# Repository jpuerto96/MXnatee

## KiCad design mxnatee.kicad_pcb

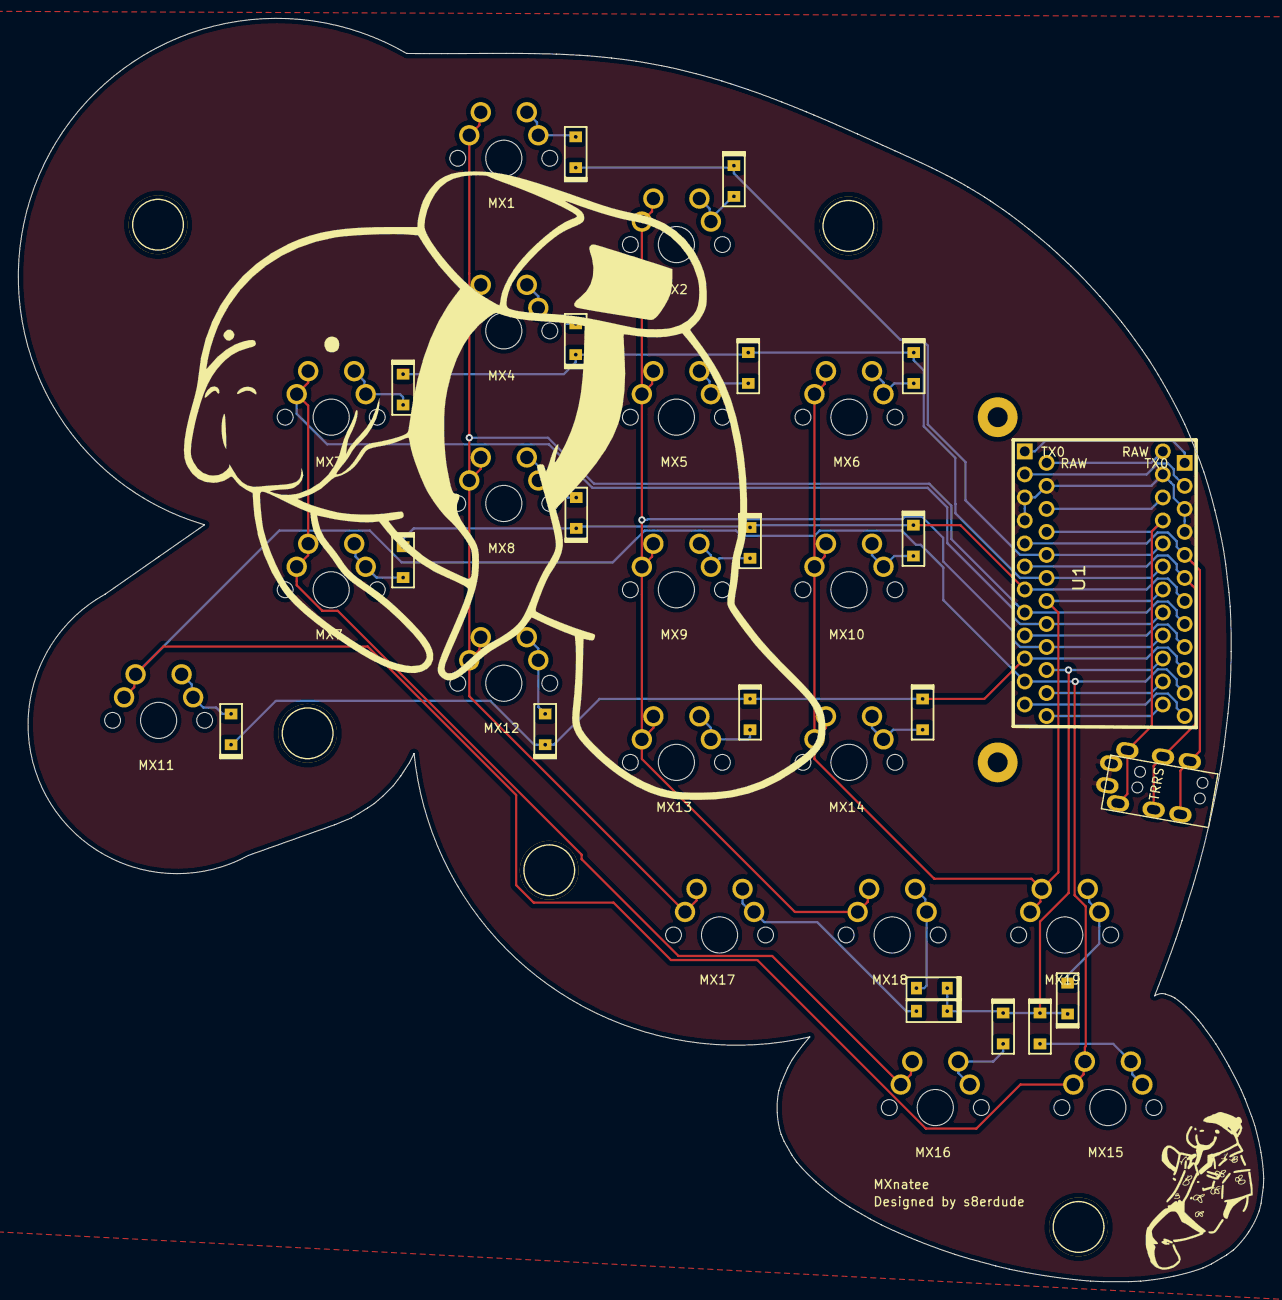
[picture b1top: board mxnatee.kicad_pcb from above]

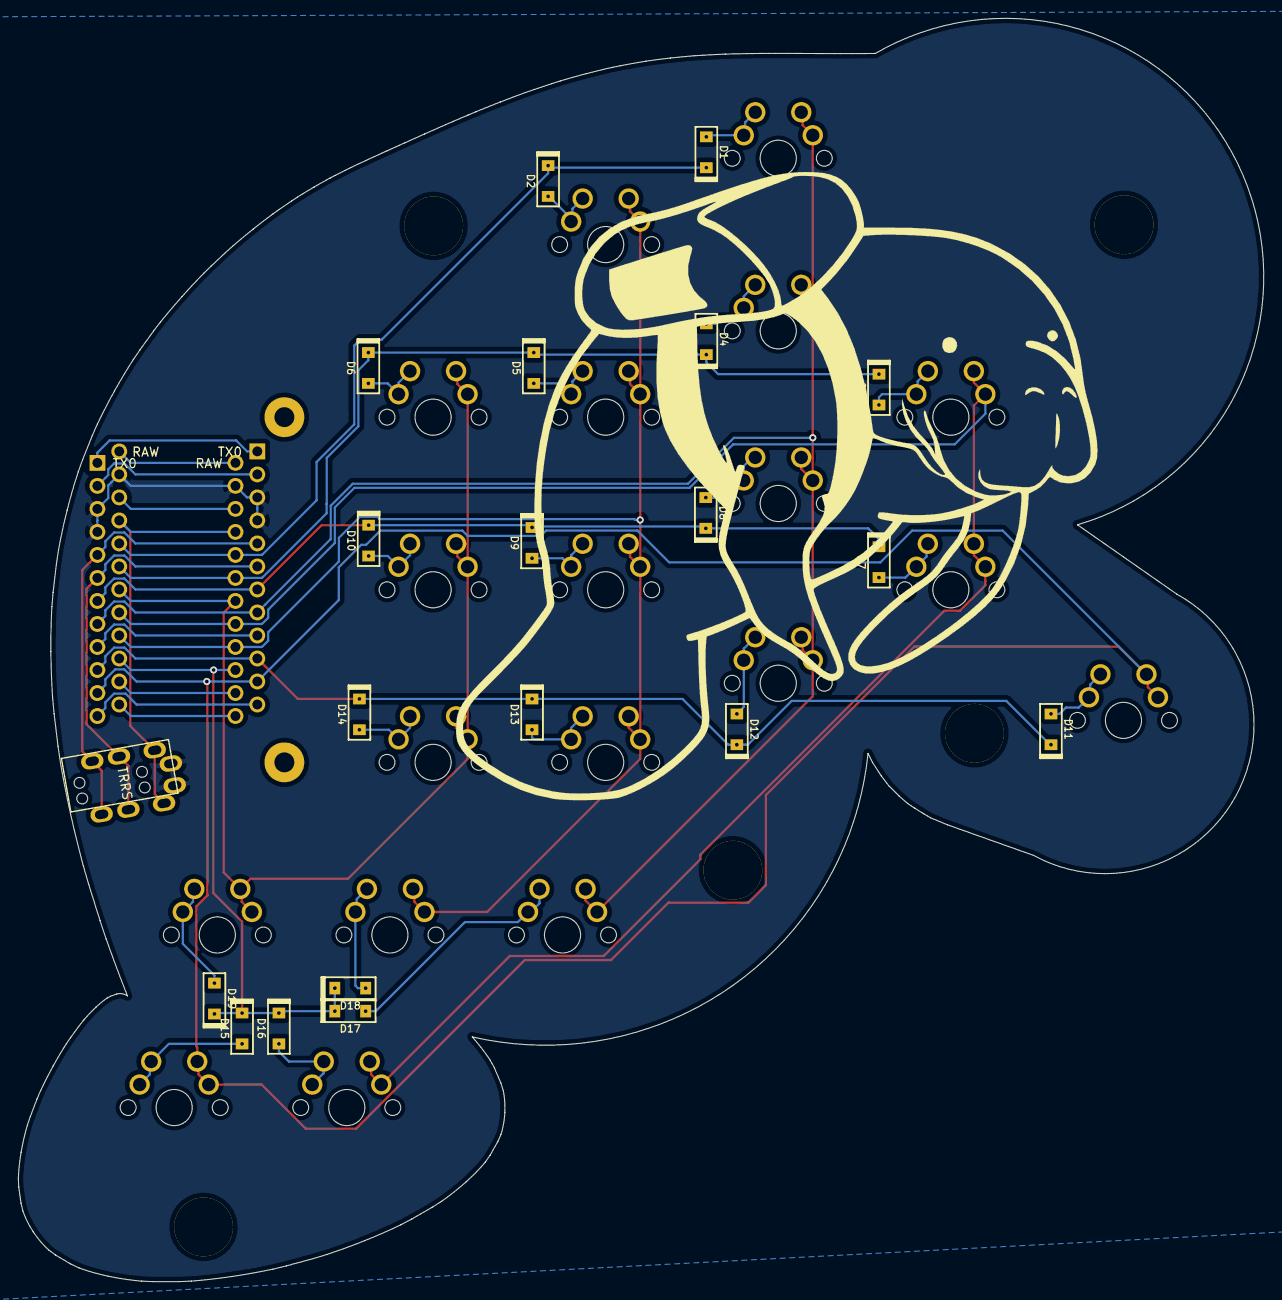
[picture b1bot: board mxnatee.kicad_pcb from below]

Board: 2 copper layers, 137.5 x 139.4 mm, 45 parts (19 on the bottom side), 33 nets.

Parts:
D1, D2, D3, D4, D5, D6, D7, D8, D9, D10, D11, D12, D13, D14, D15, D16, D17, D18, D19: D_Small; D_SOD123_thruhole
MX1, MX2, MX3, MX4, MX5, MX6, MX7, MX8, MX9, MX10, MX11, MX12, MX13, MX14, MX15, MX16, MX17, MX18, MX19: MX-NoLED; MX-NoLED-Reversible
U1: ProMicro; ArduinoProMicro-Reversible
U2: TRRS; MJ-4PP-9
U4, U4#2, U4#3, U4#4, U4#5: HOLE; MountingHole

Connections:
COL0: MX11.1, MX15.1, U1.11
COL1: MX3.1, MX7.1, MX16.1, U1.17
COL2: MX1.1, MX4.1, MX8.1, MX12.1, MX17.1, U1.8
COL3: MX2.1, MX5.1, MX9.1, MX13.1, MX18.1, U1.16
COL4: MX6.1, MX10.1, MX14.1, MX19.1, U1.18
DATA1: U1.6, U2.3
DATA2: U1.5, U2.4
GND: U1.3, U1.4, U1.23, U2.1
unnamed: D1.2, MX1.2
unnamed: D2.2, MX2.2
unnamed: D3.2, MX3.2
unnamed: D4.2, MX4.2
unnamed: D5.2, MX5.2
unnamed: D6.2, MX6.2
unnamed: D7.2, MX7.2
unnamed: D8.2, MX8.2
unnamed: D9.2, MX9.2
unnamed: D10.2, MX10.2
unnamed: D11.2, MX11.2
unnamed: D12.2, MX12.2
unnamed: D13.2, MX13.2
unnamed: D14.2, MX14.2
unnamed: D15.2, MX15.2
unnamed: D16.2, MX16.2
unnamed: D17.2, MX17.2
unnamed: D18.2, MX18.2
unnamed: D19.2, MX19.2
ROW0: D1.1, D2.1, U1.20
ROW1: D3.1, D4.1, D5.1, D6.1, U1.19
ROW2: D7.1, D8.1, D9.1, D10.1, U1.7
ROW3: D11.1, D12.1, D13.1, D14.1, U1.10
ROW4: D15.1, D16.1, D17.1, D18.1, D19.1, U1.15
VCC: U1.21, U2.2

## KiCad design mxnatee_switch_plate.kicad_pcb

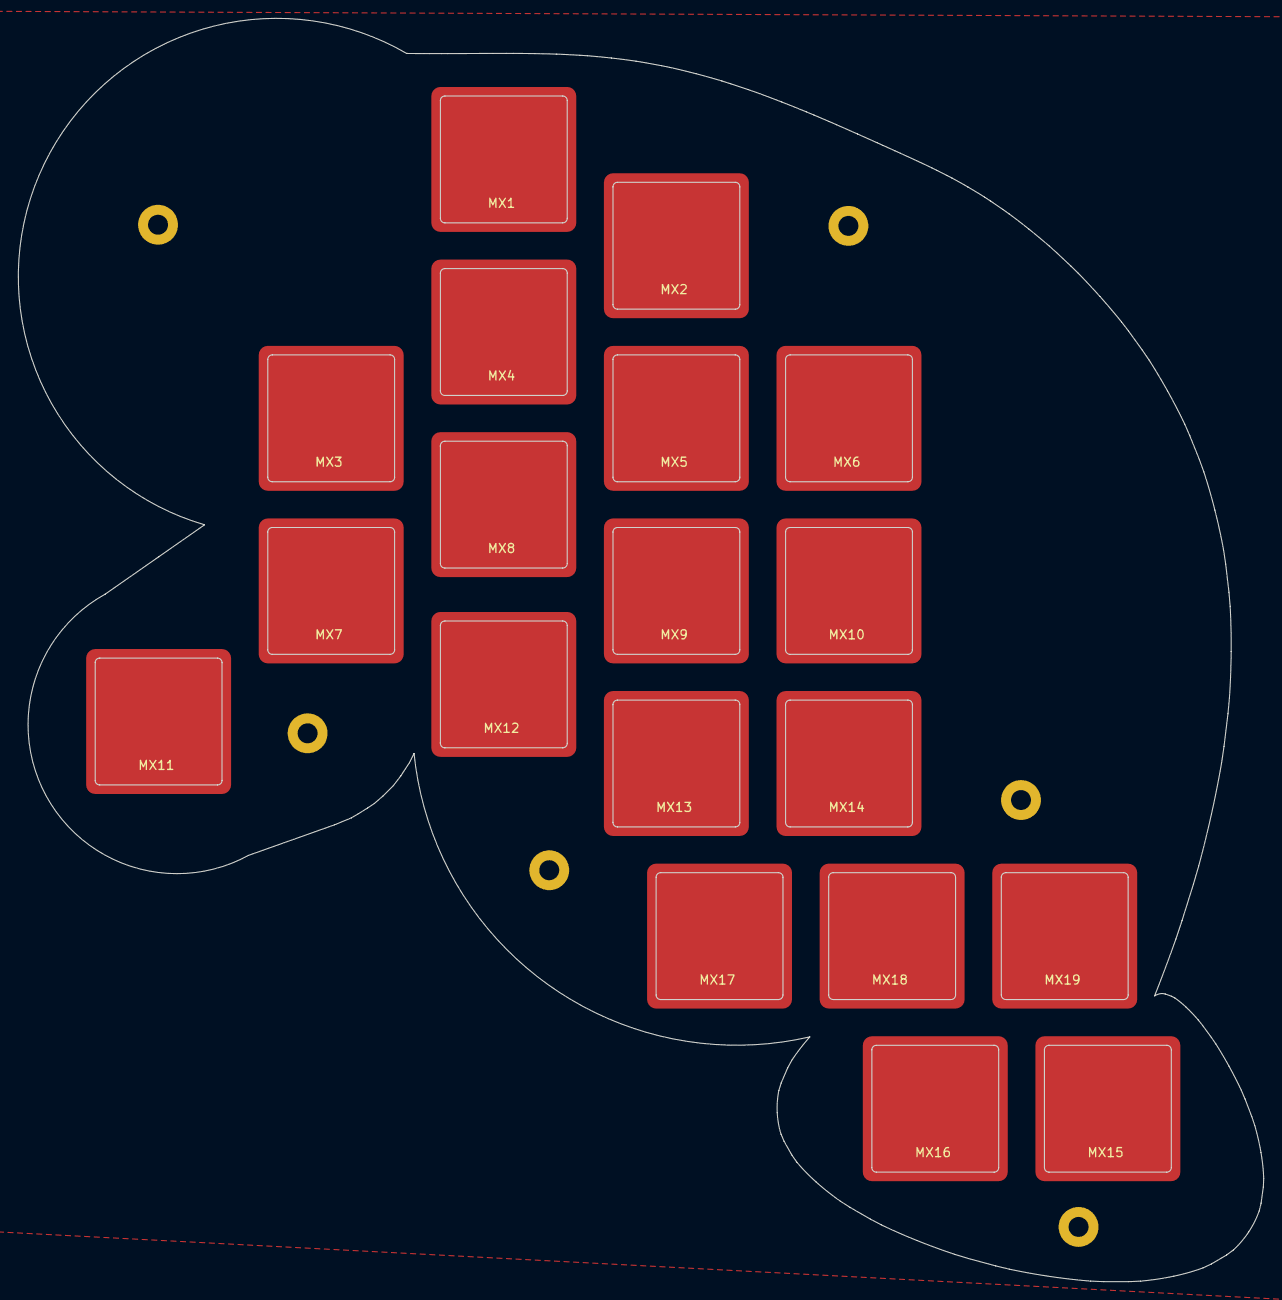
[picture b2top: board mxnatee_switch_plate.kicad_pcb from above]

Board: 2 copper layers, 137.5 x 139.4 mm, 25 parts (0 on the bottom side), 5 nets, no tracks yet.

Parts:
MX1, MX2, MX3, MX4, MX5, MX6, MX7, MX8, MX9, MX10, MX11, MX12, MX13, MX14, MX15, MX16, MX17, MX18, MX19: MX-NoLED; MX_Cutout_1u
U4, U4#2, U4#3, U4#4, U4#5, U4#6: HOLE; MountingHole_2.2mm_M2_Pad_NoSilk

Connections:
COL0: MX11.1, MX15.1
COL1: MX3.1, MX7.1, MX16.1
COL2: MX1.1, MX4.1, MX8.1, MX12.1, MX17.1
COL3: MX2.1, MX5.1, MX9.1, MX13.1
COL4: MX6.1, MX10.1, MX14.1, MX19.1

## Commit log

2021-02-07 Init repo
2021-02-07 Initial attempt at doing cool edge cuts
2021-02-08 Rev 1
2021-02-08 Rev 1.1
2021-02-08 Rev 1.2
2021-03-12 uh did stuff
